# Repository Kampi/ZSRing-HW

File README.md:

# ZSRing Hardware

## Table of Contents

- [ZSRing Hardware](#zsring-hardware)
  - [Table of Contents](#table-of-contents)
  - [About](#about)
  - [Dock connector](#dock-connector)
  - [Directory structure](#directory-structure)
  - [Purchasing](#purchasing)
  - [Maintainer](#maintainer)

## About

Hardware repository for the [ZSRing]().

Please check the [wiki]() for more information about the project.

## Directory structure

- `cad`: 3D model of the complete PCB
- `docs`: All kinds of project documentation like schematics, BOM, etc.
  - `drawings`: 2D drawings for subcomponents, etc.
  - `images`
- `project`: KiCad project for the PCB

## Purchasing

Please open `ZSRing-navigate.html` and use the files listed under `purchasing` for ordering a PCB.

## Maintainer

- [Daniel Kampert](mailto:daniel.kameprt@kampis-elektroecke.de)
- [Jakob Krantz](mail@jakobkrantz.se)

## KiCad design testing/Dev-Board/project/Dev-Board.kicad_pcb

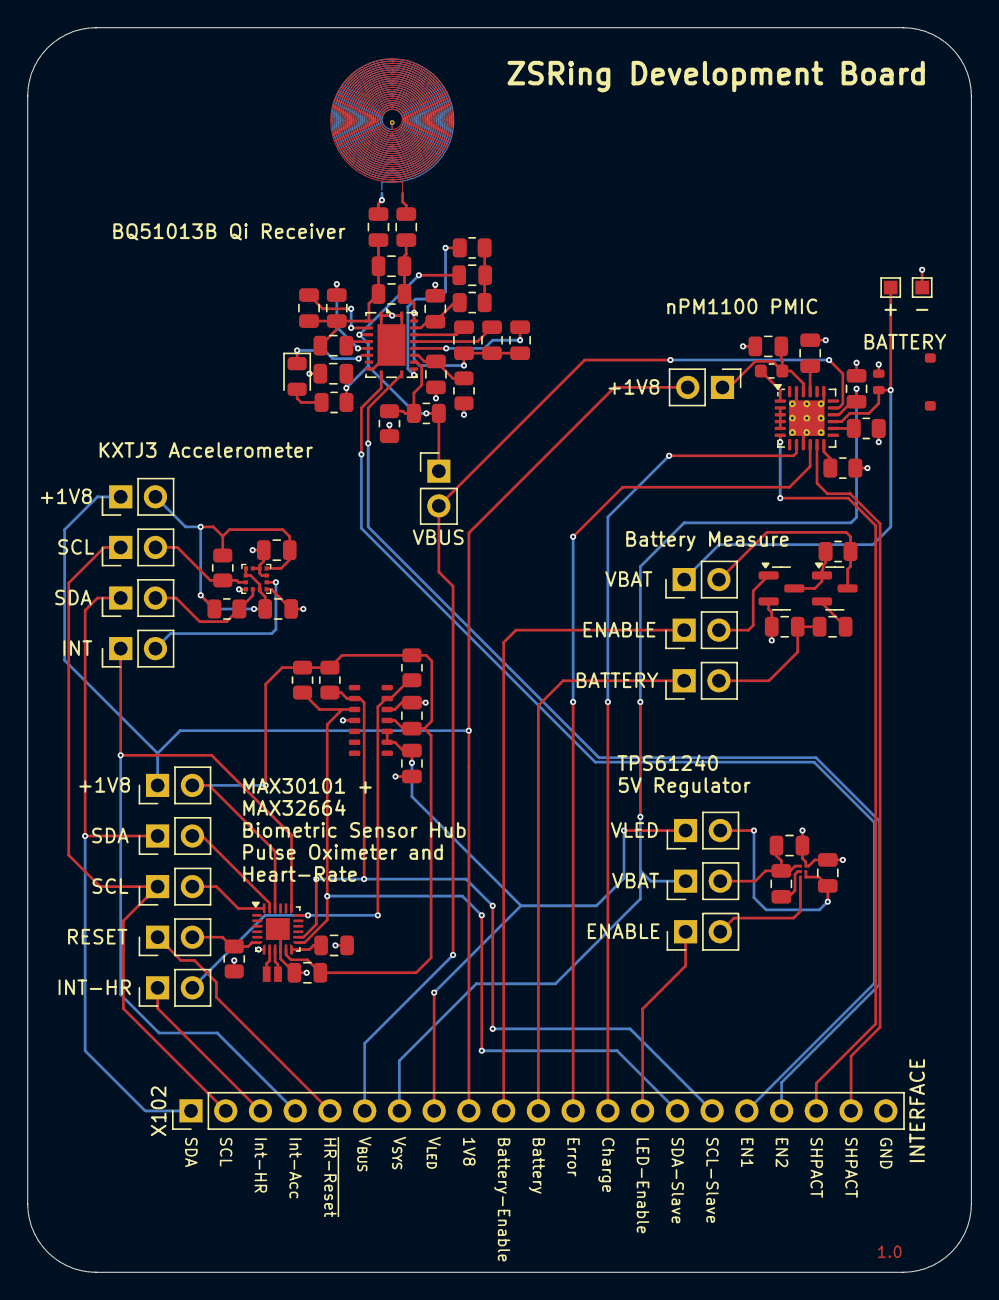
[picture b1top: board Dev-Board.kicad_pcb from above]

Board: 2 copper layers, 69.0 x 91.0 mm, 76 parts (0 on the bottom side), 65 nets.

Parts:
C101: 220n; C_0805_2012Metric
C102: C_0805_2012Metric
C103, C121: 2u2; C_0805_2012Metric
C104: 100p; C_0805_2012Metric
C105, C108: 22n; C_0805_2012Metric
C106, C107: 10n; C_0805_2012Metric
C109, C110: 470n; C_0805_2012Metric
C111, C115, C118, C119, C120: 10u; C_0805_2012Metric
C112, C114: 1u; C_0805_2012Metric
C113, C122, C123: 100n; C_0805_2012Metric
C116, C117, C124: 4u7; C_0805_2012Metric
D101: STATUS; LED_0805_2012Metric
IC101: BQ51013B; Texas_RGY_R-PVQFN-N20_EP2.05x3.05mm
IC102: MAX32664; QFN-24-1EP_3x3mm_P0.4mm_EP1.75x1.6mm
IC103: MAX30101
IC104: NPM1100-QDAA-R; QFN-24-1EP_4x4mm_P0.5mm_EP2.6x2.6mm_ThermalVias
IC105: TPS61240; DSBGA-6_0.886x1.288mm_P0.4mm
IC106: KXTJ3-1057; LGA-12_2x2mm_P0.5mm
JP101, JP114: VBAT; PinHeader_1x02_P2.54mm_Vertical
JP102, JP115: ENABLE; PinHeader_1x02_P2.54mm_Vertical
JP103: BATTERY; PinHeader_1x02_P2.54mm_Vertical
JP104: RESET; PinHeader_1x02_P2.54mm_Vertical
JP105, JP117: SDA; PinHeader_1x02_P2.54mm_Vertical
JP106, JP118: SCL; PinHeader_1x02_P2.54mm_Vertical
JP107, JP110, JP116: +1V8; PinHeader_1x02_P2.54mm_Vertical
JP108: INT-HR; PinHeader_1x02_P2.54mm_Vertical
JP109: VBUS; PinHeader_1x02_P2.54mm_Vertical
JP113: VLED; PinHeader_1x02_P2.54mm_Vertical
JP119: INT; PinHeader_1x02_P2.54mm_Vertical
L101: 7u2; Coils
L102: 2u2; L_0603_1608Metric
L103: 1u; C_0805_2012Metric
Q101: BSS138; SOT-23
Q102: BSH205G2AR; SOT-23
R101, R102: 10k; R_0805_2012Metric
R103, R104, R111: C_0805_2012Metric
R105: 196R; R_0805_2012Metric
R106: R_0805_2012Metric
R107: 18k; R_0805_2012Metric
R108, R115, R116: 1k8; R_0805_2012Metric
R109: 110R; R_0805_2012Metric
R110, R113: 1k; R_0805_2012Metric
R112: 2k; R_0805_2012Metric
R114: 4k7; R_0805_2012Metric
TH101, TH102: Thermistor_NTC; R_0805_2012Metric
TP101: +; TestPoint_Pad_1.0x1.0mm
TP102: -; TestPoint_Pad_1.0x1.0mm
X101: BATTERY; 78171-0002
X102: INTERFACE; PinHeader_1x21_P2.54mm_Vertical
Y101: 32kHz; ECS_ECX-1210

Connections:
+1V8: JP107.1 (A), JP110.2 (B), JP116.1 (A), X102.9
/Battery: JP103.1 (A), X102.11
/Battery-Enable: JP102.1 (A), X102.10
/Charge: IC104.8 (CHG), X102.13
/EN1: IC101.10 (EN1), X102.17
/EN2: IC101.11 (EN2), X102.18
/Error: IC104.10 (ERR), X102.12
/Int-Acc: IC102.19 (Int-ACC), JP119.1 (A), X102.4
/Int-HR: JP108.1 (A), X102.3
/LED-Enable: JP115.1 (A), X102.14
/SCL: JP106.1 (A), JP118.1 (A), X102.2
/SCL-Slave: IC102.14 (SCL-Sensor), IC103.2 (SCL), R108.2, X102.16
/SDA: JP105.1 (A), JP117.1 (A), X102.1
/SDA-Slave: IC102.13 (SDA-Sensor), IC103.3 (SDA), R107.2, X102.15
/SHPACT: IC104.6 (SHPACT), X102.19
/SHPHLD: IC104.11 (SHPHLD), X102.20
/V_{BAT}: IC104.15 (VBAT), JP101.1 (A), TP101.1, X101.1
/V_{BUS}: IC104.17 (VBUS), JP109.2 (B), X102.6
/V_{SYS}: C118.1, IC104.16 (VSYS), JP114.1 (A), X102.7
/~HR-Reset: JP104.1 (A), X102.5
GND: C111.2, C112.2, C113.2, C114.2, C115.2, C116.2, C117.2, C118.2, C119.2, C120.2, C121.2, C122.2, C123.1, C124.2, IC101.1 (PGND), IC101.9 (AD), IC101.20 (PGND), IC101.21 (PAD), IC102.7 (GND), IC102.10 (GND), IC102.25 (GND), IC103.4 (PGND), IC103.12 (GND), IC104.2 (VOUTBSET1), IC104.3 (VOUTBSET2), IC104.4 (AVSS), IC104.5 (ISET), IC104.7 (MODE), IC104.9 (VTERMSET), IC104.19 (D-), IC104.23 (GND), IC104.25 (EP), IC105.A2 (GND), IC106.1 (ADDR), IC106.4 (RES), IC106.6 (GND), IC106.8 (GND), IC106.9 (GND), Q101.2 (S), R101.2, R104.2, R105.1, R114.2, TH101.2, TH102.2, TP102.1, X101.2, X102.21
unnamed: C101.2, L101.2
unnamed: C102.2, L101.1
unnamed: D101.2 (A), R112.2
unnamed: D101.1 (K), IC101.7 (~CHG)
unnamed: C101.1, C103.2, C104.2, C105.2, C106.2, C110.2, IC101.2 (AC1)
unnamed: C102.1, C103.1, C104.1, C107.2, C108.2, C109.2, IC101.19 (AC2)
unnamed: C106.1, IC101.3 (BOOT1)
unnamed: C107.1, IC101.17 (BOOT2)
unnamed: C110.1, IC101.5 (CLAMP1)
unnamed: C109.1, IC101.16 (CLAMP2)
unnamed: C105.1, IC101.6 (COMM1)
unnamed: C108.1, IC101.15 (COMM2)
unnamed: C113.1, IC101.14 (FOD), R105.2
unnamed: IC101.12 (ILIM), R109.1
unnamed: C111.1, IC101.4 (OUT), JP109.1 (A), R106.2, R111.1, R112.1
unnamed: C115.1, IC101.18 (RECT), R110.1
unnamed: IC101.13 (TS-CTRL), R106.1, TH101.1
unnamed: IC102.9 (32k-In), Y101.2
unnamed: IC102.8 (32k-Out), Y101.1
unnamed: IC102.18 (Int-HR), IC103.13 (~INT), JP108.2 (B), R113.2
unnamed: IC102.24 (SCL), JP106.2 (B)
unnamed: IC102.23 (SDA), JP105.2 (B)
unnamed: C114.1, IC102.12 (V_{CORE})
unnamed: IC102.6 (~RESET), JP104.2 (B), R101.1
unnamed: C119.1, IC104.21 (DEC)
unnamed: IC104.12 (ICHG), R114.1
unnamed: IC104.14 (NTC), TH102.1
unnamed: C120.1, IC104.22 (SW), JP110.1 (A), L102.1
unnamed: IC104.1 (VOUTB), L102.2
unnamed: IC105.C1 (EN), JP115.2 (B)
unnamed: C124.1, IC105.B2 (OUT), IC105.C2 (FB), JP113.2 (B)
unnamed: C121.1, IC105.A1 (IN), JP114.2 (B), L103.1
unnamed: IC105.B1 (L), L103.2
unnamed: IC106.5 (INT), JP119.2 (B)
unnamed: IC106.12 (SCL), JP118.2 (B), R116.2
unnamed: IC106.2 (SDA), JP117.2 (B), R115.2
unnamed: JP101.2 (B), Q102.3 (D), R102.1
unnamed: JP102.2 (B), Q101.1 (G)
unnamed: JP103.2 (B), R103.2, R104.1
unnamed: Q101.3 (D), Q102.1 (G), R102.2
unnamed: Q102.2 (S), R103.1
unnamed: R109.2, R110.2, R111.2
V_{DD}: C112.1, C117.1, C122.1, C123.2, IC102.11 (V_{DD}), IC102.22 (V_{DD}), IC103.11 (V_{DD}), IC106.3 (V_{IO}), IC106.7 (V_{DD}), IC106.10 (V_{DD}), IC106.11 (V_{IO}), JP107.2 (B), JP116.2 (B), R107.1, R108.1, R113.1, R115.1, R116.1
V_{LED}: C116.1, IC103.9 (V_{LED}), IC103.10 (V_{LED}), JP113.1 (A), X102.8

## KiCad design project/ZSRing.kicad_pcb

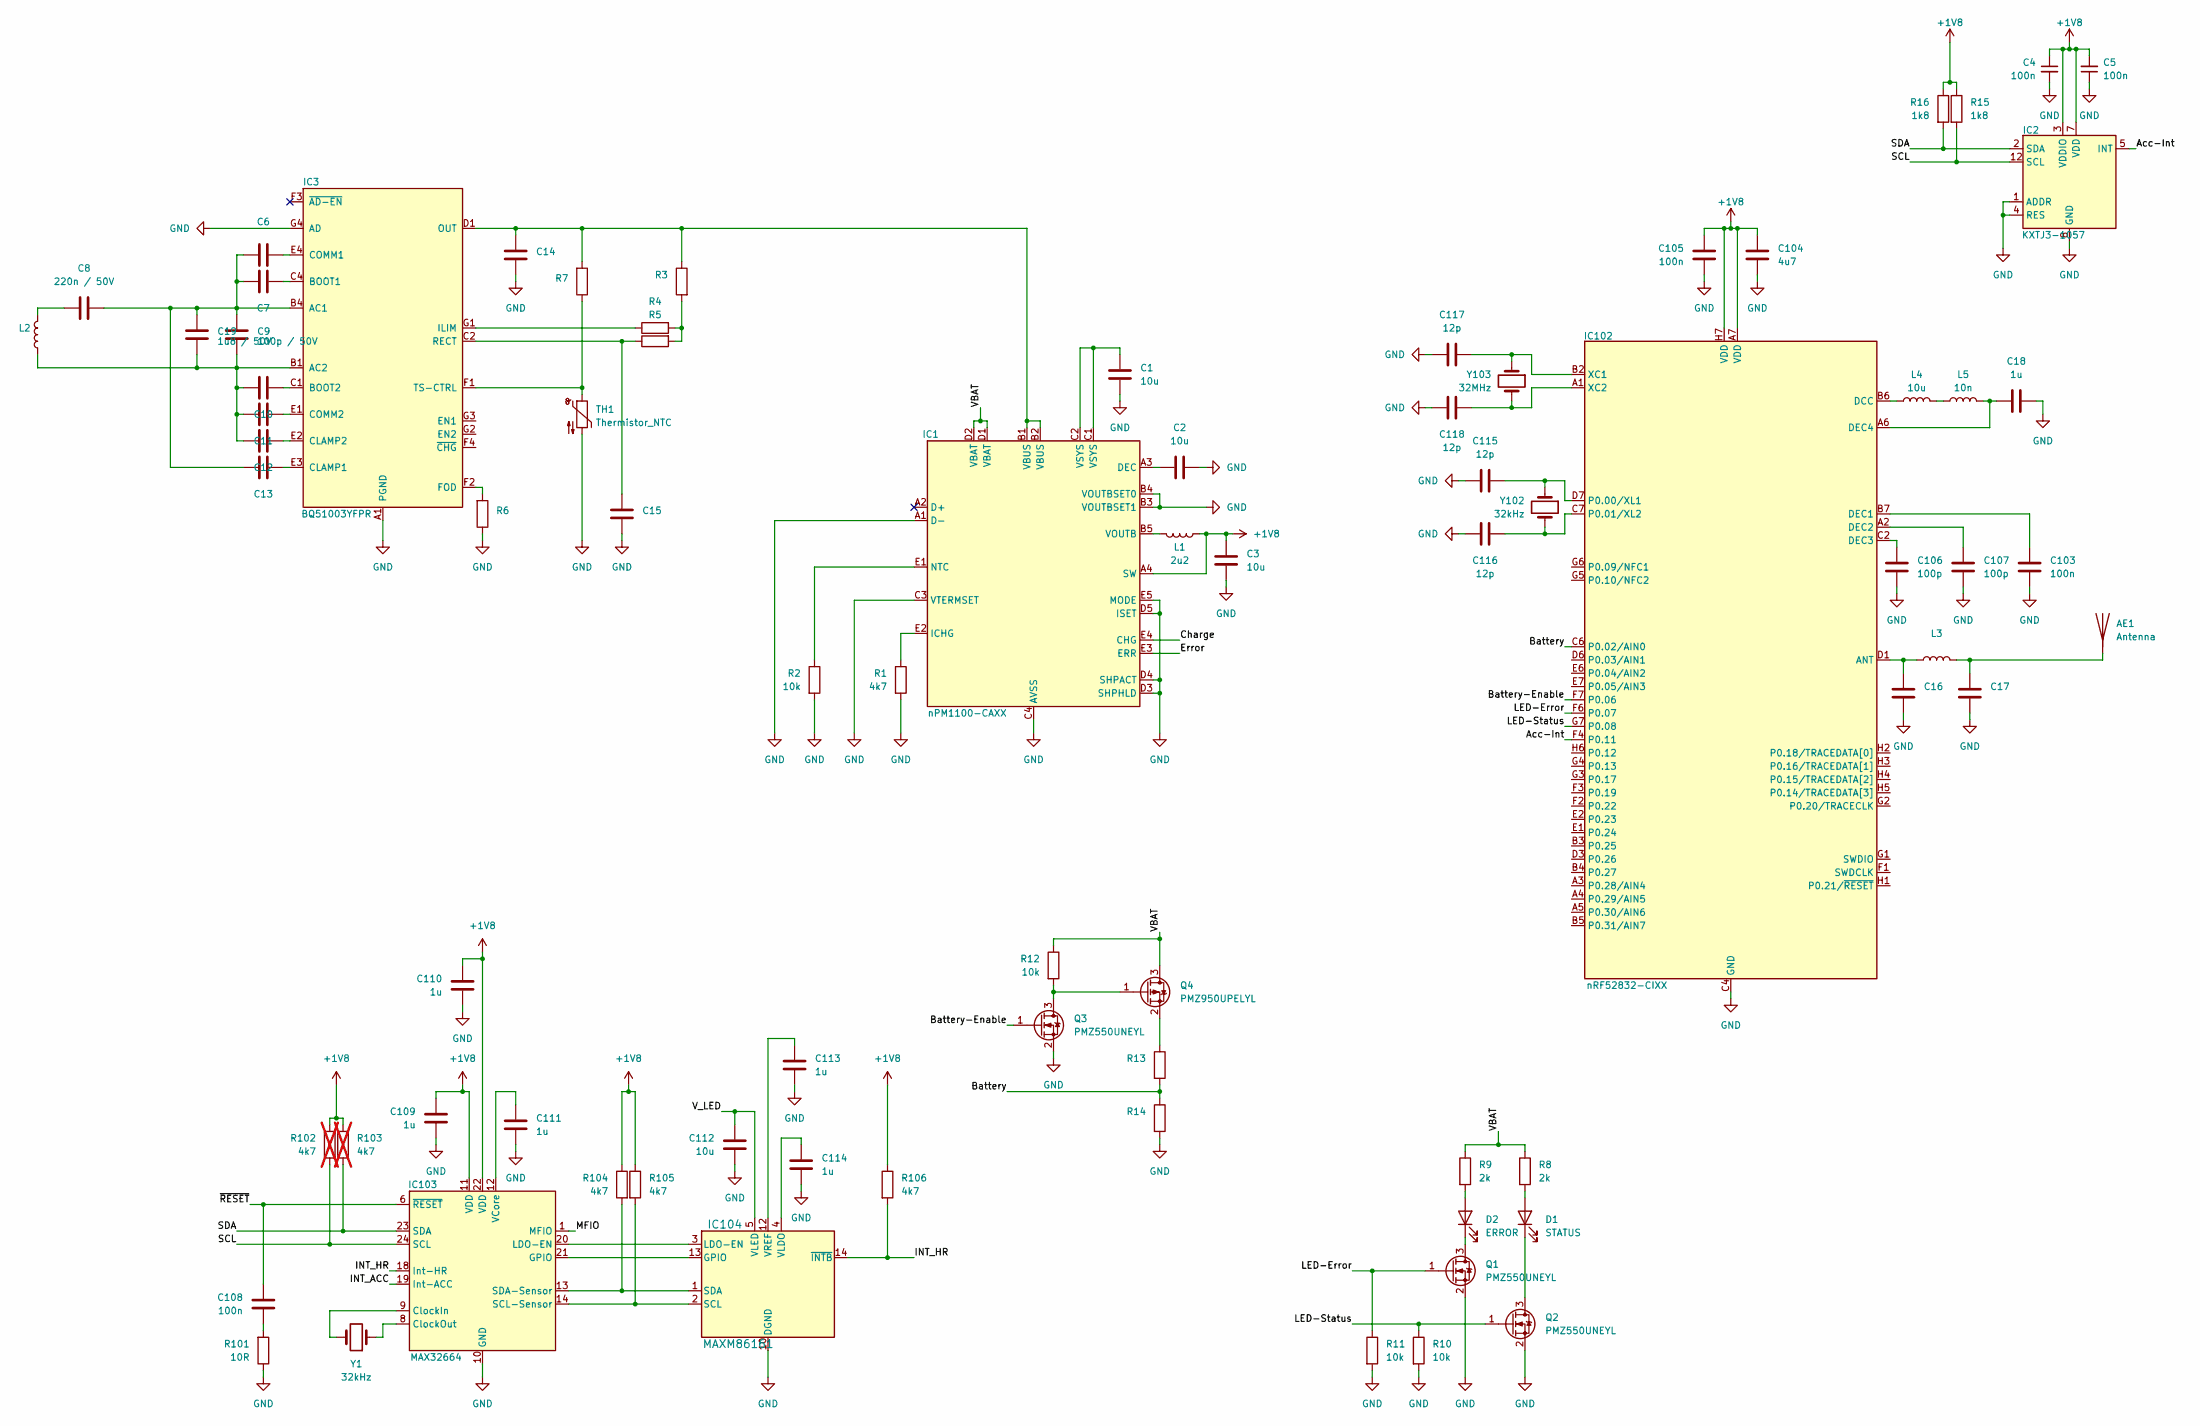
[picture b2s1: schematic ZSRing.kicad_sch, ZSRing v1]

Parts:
AE1: Antenna
C1, C2, C3, C112: 10u; C_0402_1005Metric
C4, C5, C103, C105, C108: 100n; C_0201_0603Metric
C6, C7, C10, C11, C12, C13, C14, C15, C16, C17: C_0201_0603Metric
C8: 220n / 50V; C_0603_1608Metric
C9: 100p / 50V; C_0603_1608Metric
C18, C109, C110, C111, C113, C114: 1u; C_0201_0603Metric
C19: 1u8 / 50V; C_0603_1608Metric
C104: 4u7; C_0402_1005Metric
C106, C107: 100p; C_0201_0603Metric
C115, C116, C117, C118: 12p; C_0201_0603Metric
D1: STATUS; LED_0201_0603Metric
D2: ERROR; LED_0201_0603Metric
IC1: nPM1100-CAXX; WLCSP-25_2x2mm_P0.4mm
IC2: KXTJ3-1057
IC3: BQ51003YFPR; Texas_DSBGA-28_1.9x3.0mm_Layout4x7_P0.4mm
IC102: nRF52832-CIXX; WLCSP-56_3x3.2mm_P0.4mm
IC103: MAX32664; QFN-24-1EP_3x3mm_P0.4mm_EP1.75x1.6mm
IC104: MAXM86161; MAXM8616
L1: 2u2; L_0201_0603Metric
L2: COIL
L3: (no value)
L4: 10u
L5: 10n
Q1, Q2, Q3: PMZ550UNEYL; SOT-883
Q4: PMZ950UPELYL; SOT-883
R1, R104, R105, R106: 4k7; R_0201_0603Metric
R2, R10, R11, R12: 10k; R_0201_0603Metric
R3, R4, R5, R6, R7, R13, R14: R_0201_0603Metric
R8, R9: 2k; R_0201_0603Metric
R15, R16: 1k8; R_0201_0603Metric
R101: 10R; R_0201_0603Metric
R102, R103: 4k7; R_0201_0603Metric; not fitted
TH1: Thermistor_NTC
Y1, Y102: 32kHz; ECS_ECX-1210
Y103: 32MHz; Diodes_US

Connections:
+1V8: C3.1, C4.1, C5.2, C104.1, C105.1, C109.1, C110.1, IC1.A4 (SW), IC2.3 (VDDIO), IC2.7 (VDD), IC2.10 (VDD), IC2.11 (VDDIO), IC102.A7 (VDD), IC102.H7 (VDD), IC103.11 (VDD), IC103.22 (VDD), L1.1, R15.1, R16.1, R102.1, R103.1, R104.1, R105.1, R106.1
/Acc-Int: IC2.5 (INT), IC102.F4 (P0.11)
/Battery: IC102.C6 (P0.02/AIN0), R13.2, R14.1
/Battery-Enable: IC102.F7 (P0.06), Q3.1 (G)
/Charge: IC1.E4 (CHG)
/Error: IC1.E3 (ERR)
/INT_ACC: IC103.19 (Int-ACC)
/INT_HR: IC103.18 (Int-HR), IC104.14 (~INTB), R106.2
/LED-Error: IC102.F6 (P0.07), Q1.1 (G), R11.1
/LED-Status: IC102.G7 (P0.08), Q2.1 (G), R10.1
/MFIO: IC103.1 (MFIO)
/SCL: IC2.12 (SCL), IC103.24 (SCL), R15.2, R102.2
/SDA: IC2.2 (SDA), IC103.23 (SDA), R16.2, R103.2
/VBAT: IC1.D1 (VBAT), IC1.D2 (VBAT), Q4.3 (D), R8.1, R9.1, R12.1
/V_LED: C112.1, IC104.5 (VLED)
/~RESET: C108.1, IC103.6 (~RESET)
GND: C1.2, C2.2, C3.2, C4.2, C5.1, C14.2, C15.2, C16.2, C17.2, C18.2, C103.2, C104.2, C105.2, C106.2, C107.2, C109.2, C110.2, C111.2, C112.2, C113.2, C114.2, C115.1, C116.2, C117.1, C118.2, IC1.A1 (D-), IC1.A5 (PVSS), IC1.B3 (VOUTBSET1), IC1.B4 (VOUTBSET0), IC1.C3 (VTERMSET), IC1.C4 (AVSS), IC1.C5 (AVSS), IC1.D3 (SHPHLD), IC1.D4 (SHPACT), IC1.D5 (ISET), IC1.E5 (MODE), IC2.1 (ADDR), IC2.4 (RES), IC2.6 (GND), IC2.8 (GND), IC2.9 (GND), IC3.A1 (PGND), IC3.A2 (PGND), IC3.A3 (PGND), IC3.A4 (PGND), IC3.G4 (AD), IC102.C4 (GND), IC102.C5 (GND), IC102.D2 (GND), IC102.E3 (GND), IC102.F5 (GND), IC103.7 (GND), IC103.10 (GND), IC103.25 (GND), IC104.9 (PGND), IC104.10 (DGND), IC104.11 (AGND), Q1.2 (S), Q2.2 (S), Q3.2 (S), R1.2, R2.2, R6.1, R10.2, R11.2, R14.2, R101.1, TH1.2
unnamed: AE1.1, C17.1, L3.2
unnamed: C1.1, IC1.C1 (VSYS), IC1.C2 (VSYS)
unnamed: C8.2, L2.2
unnamed: C9.2, C10.2, C11.2, C12.2, C19.2, IC3.B1 (AC2), IC3.B2 (AC2), L2.1
unnamed: C6.2, C7.2, C8.1, C9.1, C13.2, C19.1, IC3.B3 (AC1), IC3.B4 (AC1)
unnamed: C14.1, IC1.B1 (VBUS), IC1.B2 (VBUS), IC3.D1 (OUT), IC3.D2 (OUT), IC3.D3 (OUT), IC3.D4 (OUT), R3.1, R7.2
unnamed: C15.1, IC3.C2 (RECT), IC3.C3 (RECT), R5.1
unnamed: C108.2, R101.2
unnamed: D1.2 (A), R8.2
unnamed: D1.1 (K), Q2.3 (D)
unnamed: D2.2 (A), R9.2
unnamed: D2.1 (K), Q1.3 (D)
unnamed: C2.1, IC1.A3 (DEC)
unnamed: IC1.E2 (ICHG), R1.1
unnamed: IC1.E1 (NTC), R2.1
unnamed: IC1.B5 (VOUTB), L1.2
unnamed: C7.1, IC3.C4 (BOOT1)
unnamed: C10.1, IC3.C1 (BOOT2)
unnamed: C13.1, IC3.E3 (CLAMP1)
unnamed: C12.1, IC3.E2 (CLAMP2)
unnamed: C6.1, IC3.E4 (COMM1)
unnamed: C11.1, IC3.E1 (COMM2)
unnamed: IC3.F2 (FOD), R6.2
unnamed: IC3.G1 (ILIM), R4.1
unnamed: IC3.F1 (TS-CTRL), R7.1, TH1.1
unnamed: C16.1, IC102.D1 (ANT), L3.1
unnamed: IC102.B6 (DCC), L4.1
unnamed: C103.1, IC102.B7 (DEC1)
unnamed: C107.1, IC102.A2 (DEC2)
unnamed: C106.1, IC102.C2 (DEC3)
unnamed: C18.1, IC102.A6 (DEC4), L5.2
unnamed: C115.2, IC102.D7 (P0.00/XL1), Y102.1
unnamed: C116.1, IC102.C7 (P0.01/XL2), Y102.2
unnamed: C117.2, IC102.B2 (XC1), Y103.1
unnamed: C118.1, IC102.A1 (XC2), Y103.2
unnamed 52: IC103.9 (ClockIn), Y1.2; also elsewhere on the board
unnamed 53: IC103.8 (ClockOut), Y1.1; also elsewhere on the board
unnamed: IC103.21 (GPIO), IC104.13 (GPIO)
unnamed: IC103.20 (LDO-EN), IC104.3 (LDO-EN)
unnamed: IC103.14 (SCL-Sensor), IC104.2 (SCL), R105.2
unnamed: IC103.13 (SDA-Sensor), IC104.1 (SDA), R104.2
unnamed: C111.1, IC103.12 (VCore)
unnamed: C114.1, IC104.4 (VLDO)
unnamed: C113.1, IC104.12 (VREF)
unnamed: L4.2, L5.1
unnamed: Q3.3 (D), Q4.1 (G), R12.2
unnamed: Q4.2 (S), R13.1
unnamed: R3.2, R4.2, R5.2

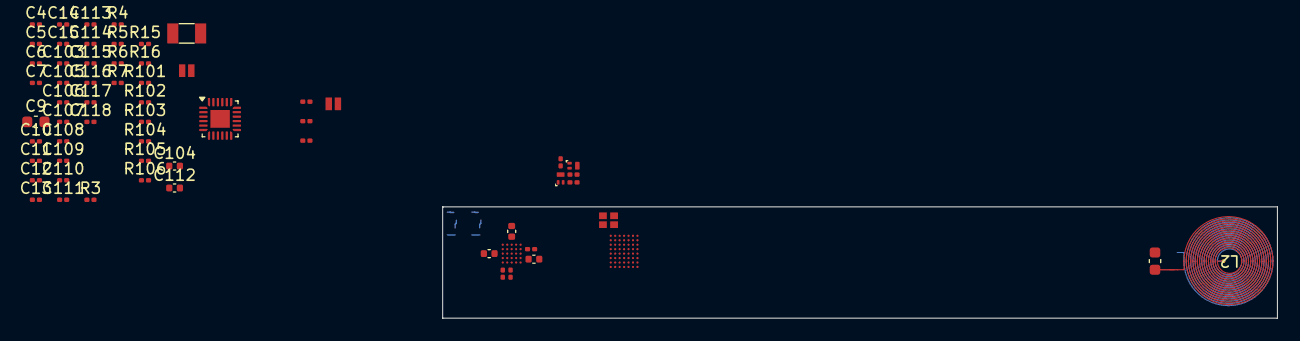
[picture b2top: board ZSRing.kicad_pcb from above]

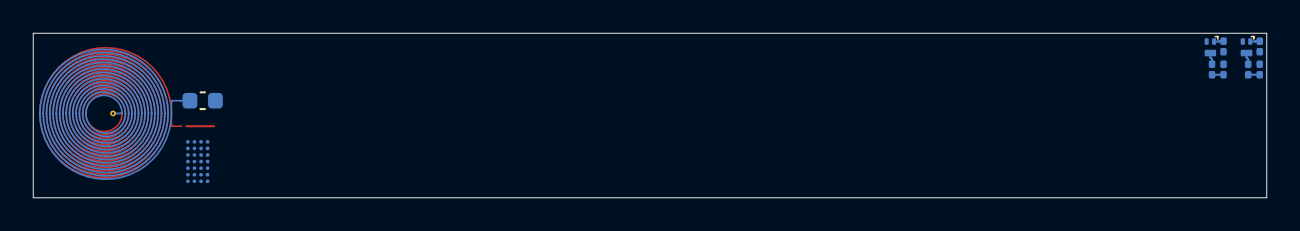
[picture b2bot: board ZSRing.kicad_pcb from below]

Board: 2 copper layers, 75.0 x 10.0 mm, 73 parts (10 on the bottom side), 52 nets.

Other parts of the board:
Y101: 32kHz; Crystal_SMD_3215-2Pin_3.2x1.5mm

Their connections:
unnamed 52: Y101.1; also elsewhere on the board
unnamed 53: Y101.2; also elsewhere on the board

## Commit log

2024-10-23 Initialize repo
2024-10-23 Initialize branch
2024-10-24 Working on HW revision 1
2024-10-29 Add ZSRing Dev-Board
2024-10-31 Add layout for Dev-Board
2024-11-05 Changes from Jakob
2024-11-07 Cosmetic changes only. Silkscreen and edge cuts.

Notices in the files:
README.md:
License: GPL 3.0
